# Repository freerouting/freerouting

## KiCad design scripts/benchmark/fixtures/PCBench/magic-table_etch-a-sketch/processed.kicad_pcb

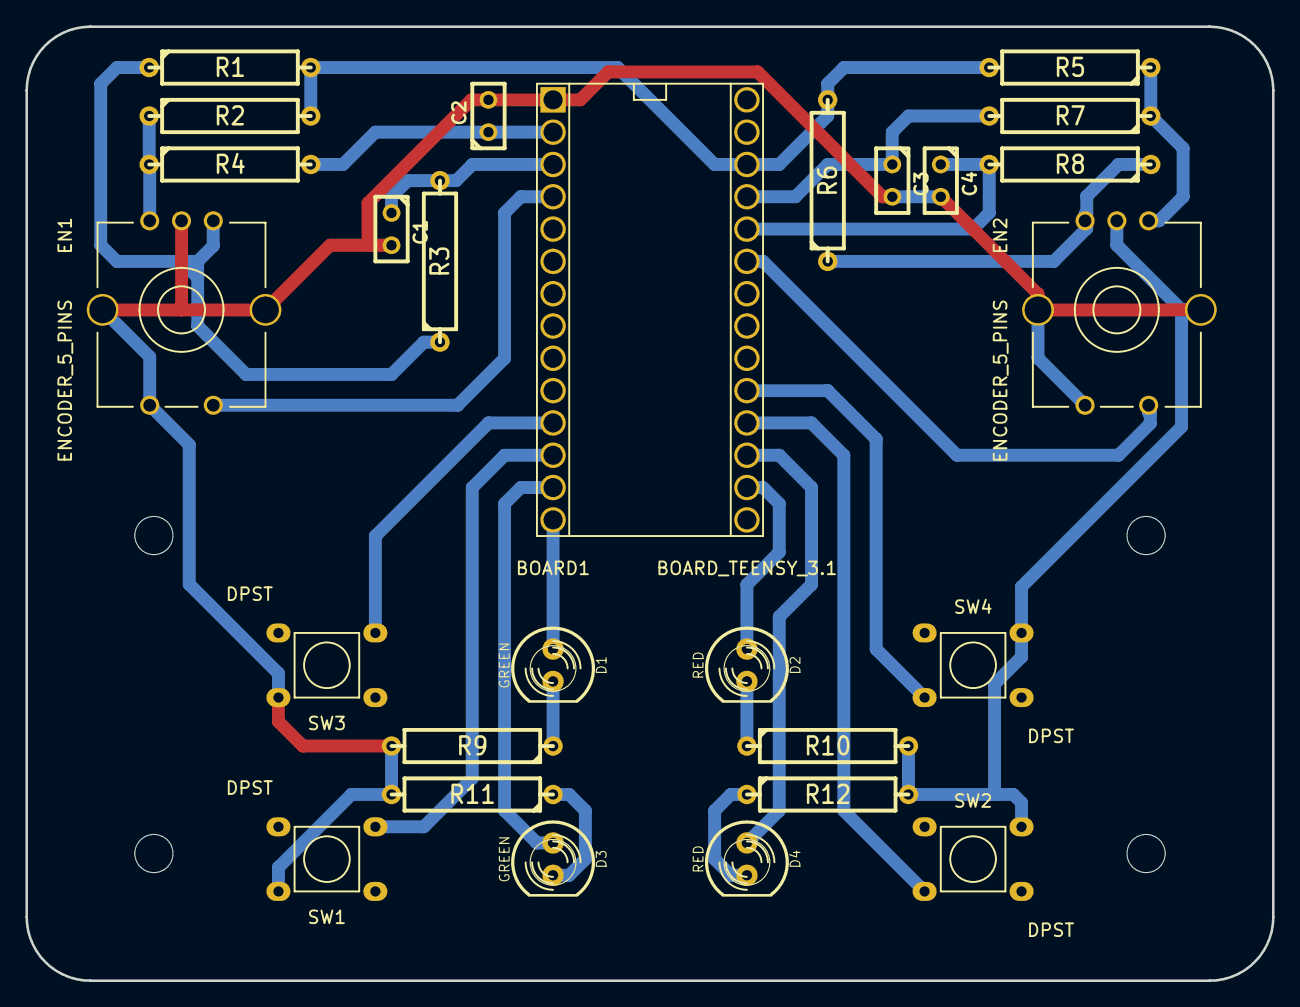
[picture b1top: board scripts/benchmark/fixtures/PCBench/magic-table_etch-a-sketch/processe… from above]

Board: 2 copper layers, 98.0 x 75.0 mm, 31 parts (0 on the bottom side), 24 nets.

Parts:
BOARD1: BOARD_TEENSY_3.1; Board_Teensy_3_1
C1, C2, C3, C4: C; C1
D1, D3: GREEN; LED-5MM
D2, D4: RED; LED-5MM
EN1, EN2: ENCODER_5_PINS; Misc_Encoder_5_Pins_w_shield
Mechanical_drill_3mm, Mechanical_drill_3mm_2, Mechanical_drill_3mm_3, Mechanical_drill_3mm_4: Mechanical_drill_3mm
R1, R2, R3, R4, R5, R6, R7, R8, R9, R10, R11, R12: R; R5
SW1, SW2, SW3, SW4: DPST; Switches-Push_switch_THD

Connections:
/D0: BOARD1.2, C2.1, R4.2
/D1: BOARD1.3, C1.1, R3.2
/D2: BOARD1.4, EN1.4
/D9: BOARD1.11, SW3.3
/D10: BOARD1.12, SW1.3
/D11: BOARD1.13, D3.1
/D12: BOARD1.14, D1.1
/D14: BOARD1.16, D2.1
/D15: BOARD1.17, D4.1
/D16: BOARD1.18, SW2.3
/D17: BOARD1.19, SW4.3
/D21: BOARD1.23, EN2.4
/D22: BOARD1.24, C4.1, R8.2
/D23: BOARD1.25, C3.1, R7.2
GND: BOARD1.1, C1.2, C2.2, C3.2, C4.2, EN1.2, EN1.5, EN1.SHLD, EN2.2, EN2.5, EN2.SHLD, R9.2, R10.2, R11.2, R12.2, SW1.2, SW2.2, SW3.2, SW4.2
unnamed: D2.2, R10.1
unnamed: D4.2, R12.1
unnamed: D3.2, R11.1
unnamed: D1.2, R9.1
unnamed: EN2.1, R5.1, R7.1
unnamed: EN1.1, R1.1, R3.1
unnamed: EN1.3, R2.1, R4.1
unnamed: EN2.3, R6.1, R8.1
VCC: BOARD1.26, R1.2, R2.2, R5.2, R6.2

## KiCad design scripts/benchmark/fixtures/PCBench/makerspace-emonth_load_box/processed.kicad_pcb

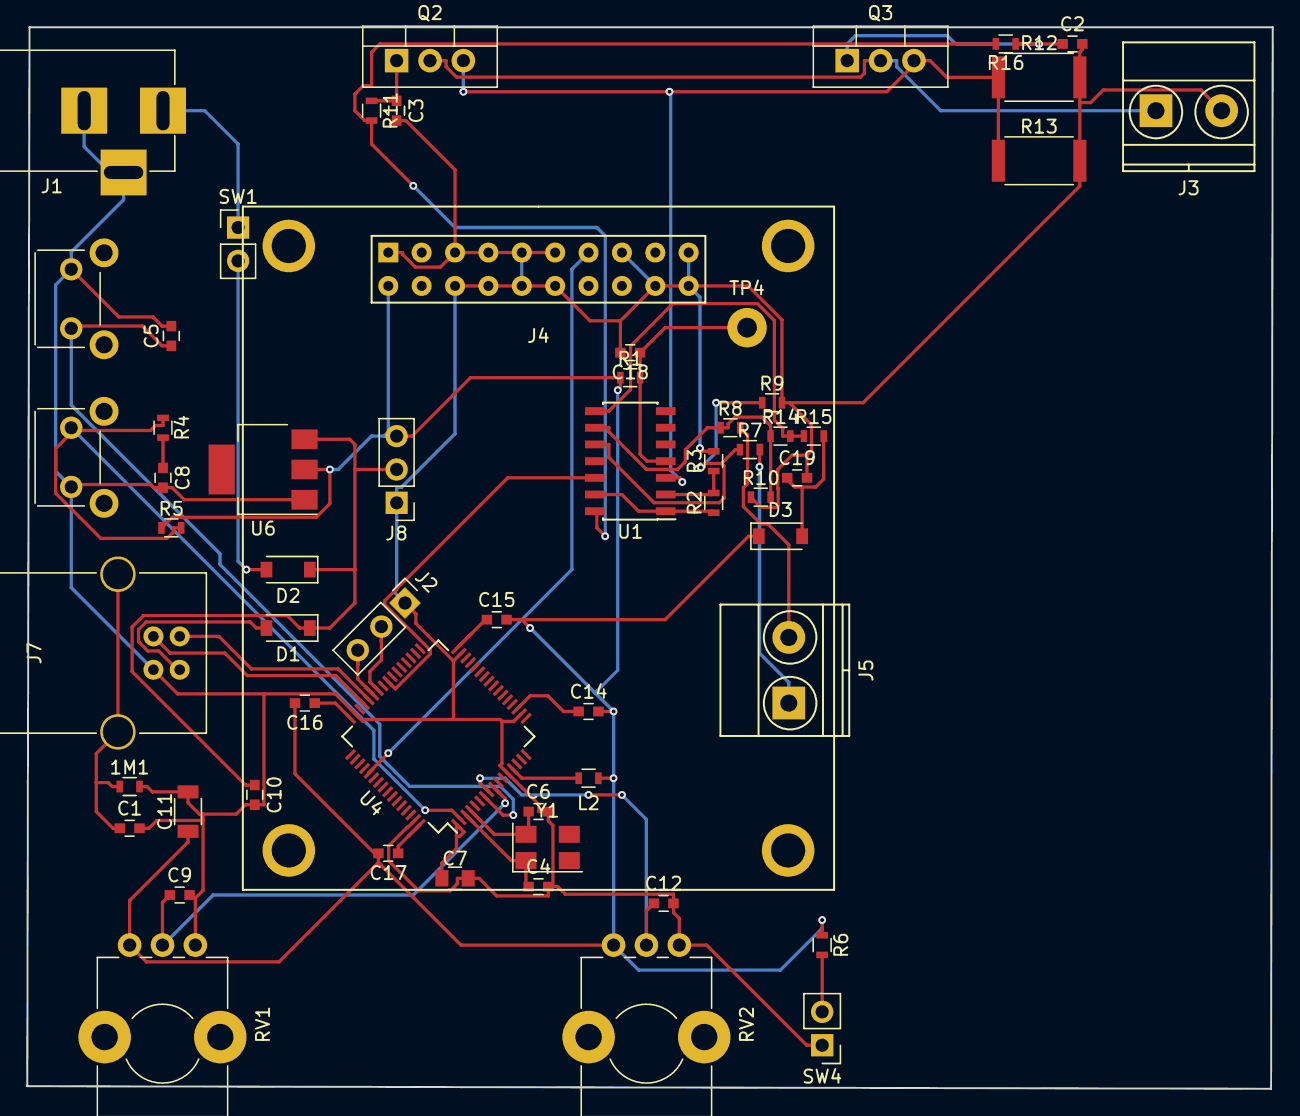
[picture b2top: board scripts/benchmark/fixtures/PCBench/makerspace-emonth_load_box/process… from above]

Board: 2 copper layers, 94.8 x 80.8 mm, 59 parts (0 on the bottom side), 41 nets.

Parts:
1M1: R; R_0603
C1: 4n7; C_0603
C2, C3, C5, C8, C9, C12, C18: 0.1; C_0603
C4, C6, C14, C15, C16, C17: C; C_0603
C7: 1.0; C_0805
C10: 0.1u; C_0603
C11: 10u; C_1206
C19: 4.7n; C_0603
D1, D2: D; D_SOD-123
D3: D_Schottky; D_SOD-123
J1: BARREL_JACK
J2, J8: CONN_01X03; Socket_Strip_Straight_1x03_Pitch2.54mm
J3, J5: Screw_Terminal_1x02; TerminalBlock_Pheonix_MKDS1.5-2pol
J4: CONN_02X10; NHD-1.69
J7: USB_B
L2: Ferrite_Bead; L_0603
Q2, Q3: FQP30N06L; TO-220_Vertical
R1, R4, R11, R16: 100R; R_0603
R2: 24K; R_0603
R3, R6, R9, R14: 10K; R_0603
R5, R10: 4.7K; R_0603
R7, R8, R15: 100K; R_0603
R12, R13: 0R1; R_2512
RV1, RV2: POT; Potentiometer_Alps_RK09K_Horizontal
SW1: SW_SPST; Socket_Strip_Straight_1x02_Pitch2.54mm
SW2, SW3: SW_Push; SW_Tactile_SKHH_Angled
SW4: SW_Push; Pin_Header_Straight_1x02_Pitch2.54mm
TP4: TEST; Measurement_Point_Round-TH_Big
U1: LM324; SOIC-14_3.9x8.7mm_Pitch1.27mm
U4: STM32L152RCTx; LQFP-64_10x10mm_Pitch0.5mm
U6: LD1117S33TR; SOT-223
Y1: Crystal_GND23; Crystal_SMD_5032-4pin_5.0x3.2mm

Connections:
+3V3: C11.1, C14.2, C15.2, C16.2, C17.2, D3.1, J4.2, J8.3, L2.1, R1.1, R5.1, R6.1, RV1.1, RV2.1, U6.2
+12V: D2.2, SW1.2
+BATT: C10.1, D1.1, D2.1, J8.2, U6.3
/load_box_display/MOSI: J4.13, U4.53
/load_box_interface/GO_BUTTON: R6.2, SW4.2
/load_box_interface/STATIC_VREF: C12.1, RV2.2, U4.8
/load_box_interface/STEP_VREF: C9.1, RV1.2, U4.9
/load_box_interface/USER_BUTTON: R4.1, R5.2, SW3.1, U4.2
/load_box_mcu/CHOSEN_VREF: U1.12, U4.40
/load_box_mcu/USB_DM: J7.2, U4.44
/load_box_mcu/USB_DP: J7.3, U4.45
/load_box_sink/REMOTE_SENSE_OUT: C19.1, D3.2, R15.2
GND: 1M1.2, C1.2, C2.2, C3.2, C4.2, C5.2, C6.2, C7.2, C8.2, C9.2, C10.2, C11.2, C12.2, C18.2, C19.2, J1.2, J1.3, J2.1, J3.2, J4.1, J4.5, J4.6, J4.7, J4.8, J4.9, J4.10, J4.11, J4.12, J4.15, J4.18, J4.19, J4.20, J7.4, J8.1, R3.2, R9.2, R10.1, R12.2, R13.2, RV1.3, RV2.3, SW2.1, SW3.2, SW4.1, U4.12, U4.18, U4.31, U4.47, U4.63, U6.1
NRST: C5.1, SW2.2, U4.7
unnamed: 1M1.1, C1.1, J7.5
unnamed: C2.1, Q3.1, R16.1
unnamed: C3.1, Q2.1, R11.1
unnamed: C4.1, U4.3, Y1.1
unnamed: C6.1, U4.4, Y1.4
unnamed: C7.1, U4.1
unnamed: C8.1, R4.2
unnamed: C14.1, U4.19
unnamed: C15.1, U4.32
unnamed: C16.1, U4.48
unnamed: C17.1, U4.64
unnamed: C18.1, R1.2, TP4.1, U1.4
unnamed: D1.2, J7.1
unnamed: J1.1, SW1.1
unnamed: J2.2, U4.42
unnamed: J2.3, U4.43
unnamed: J3.1, Q2.2, Q3.2
unnamed: J5.1, R7.2
unnamed: J5.2, R8.2
unnamed: L2.2, U4.13
unnamed: Q2.3, Q3.3, R12.1, R13.1, U1.3
unnamed: R2.1, U1.1, U1.13
unnamed: R2.2, R3.1, U1.2
unnamed: R7.1, R9.1, U1.10
unnamed: R8.1, R10.2, R14.1, U1.9
unnamed: R11.2, R16.2, U1.14
unnamed: R14.2, R15.1, U1.8
